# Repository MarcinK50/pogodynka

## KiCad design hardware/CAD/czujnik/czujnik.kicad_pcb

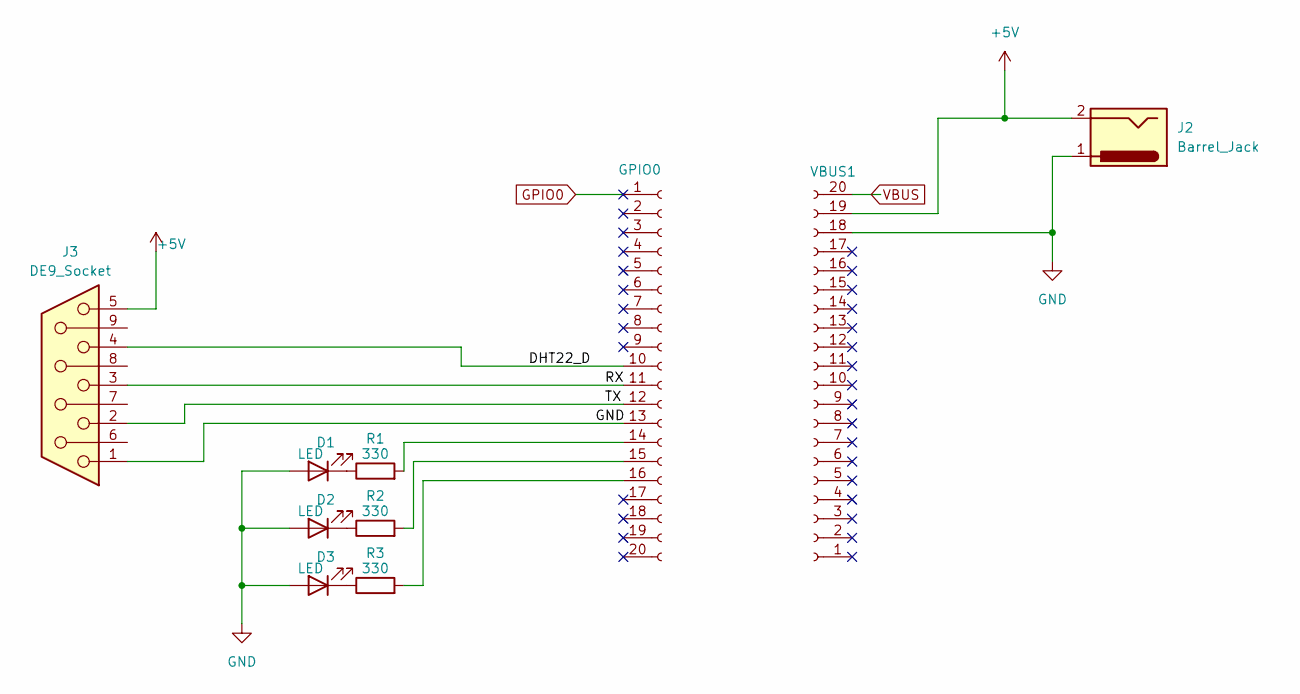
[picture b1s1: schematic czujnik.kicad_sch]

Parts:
D1, D2, D3: LED; LED_D3.0mm_Clear
GPIO0: Conn_01x20_Socket; PinSocket_1x20_P2.54mm_Vertical
J2: Barrel_Jack; BarrelJack_CUI_PJ-063AH_Horizontal_CircularHoles
J3: DE9_Socket; DSUB-9_Socket_Horizontal_P2.77x2.84mm_EdgePinOffset7.70mm_H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
R1, R2, R3: 330; R_Axial_DIN0207_L6.3mm_D2.5mm_P10.16mm_Horizontal
VBUS1: Conn_01x20_Socket; PinSocket_1x20_P2.54mm_Vertical

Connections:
+5V: J2.2, J3.5, VBUS1.19; also elsewhere on the board
/DHT22_D: GPIO0.10, J3.4
/RX: GPIO0.11, J3.3
/TX: GPIO0.12, J3.2
GND: D1.2 (A), D2.2 (A), D3.2 (A), GPIO0.13, J2.1, J3.1, VBUS1.18; also elsewhere on the board
GPIO0: GPIO0.1
unnamed: D1.1 (K), R1.1
unnamed: D2.1 (K), R2.1
unnamed: D3.1 (K), R3.1
unnamed: GPIO0.14, R1.2
unnamed: GPIO0.15, R2.2
unnamed: GPIO0.16, R3.2

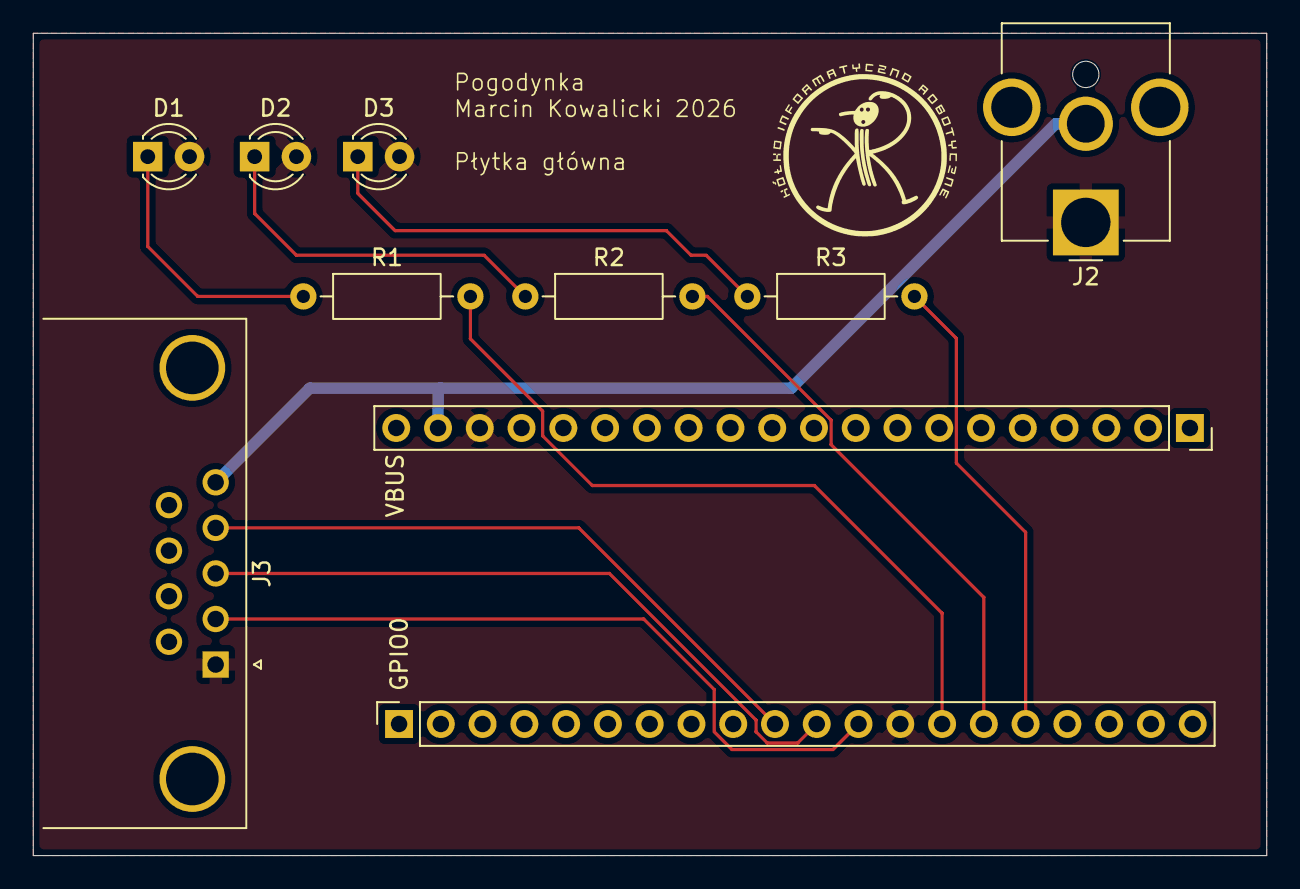
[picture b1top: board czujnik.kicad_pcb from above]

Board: 2 copper layers, 75.0 x 50.0 mm, 10 parts (0 on the bottom side), 11 nets.

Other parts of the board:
VBUS: Conn_01x20_Socket; PinSocket_1x20_P2.54mm_Vertical

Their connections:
+5V: VBUS.19; also elsewhere on the board
GND: VBUS.18; also elsewhere on the board

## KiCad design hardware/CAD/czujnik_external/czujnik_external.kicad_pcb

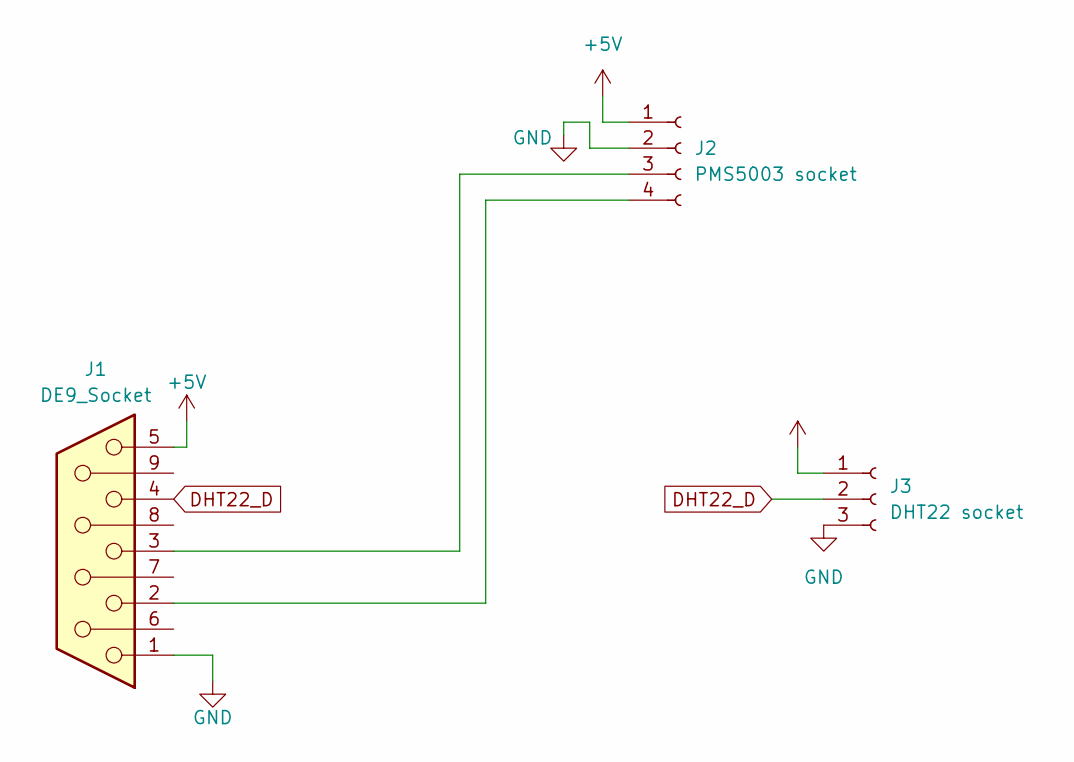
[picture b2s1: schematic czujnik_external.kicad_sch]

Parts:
J1: DE9_Socket; DSUB-9_Socket_Horizontal_P2.77x2.54mm_EdgePinOffset9.40mm
J2: PMS5003 socket; PinSocket_1x04_P2.54mm_Vertical
J3: DHT22 socket; PinSocket_1x03_P2.54mm_Vertical

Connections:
+5V: J1.5, J2.1, J3.1
DHT22_D: J1.4, J3.2
GND: J1.1, J2.2, J3.3
unnamed: J1.3, J2.3
unnamed: J1.2, J2.4

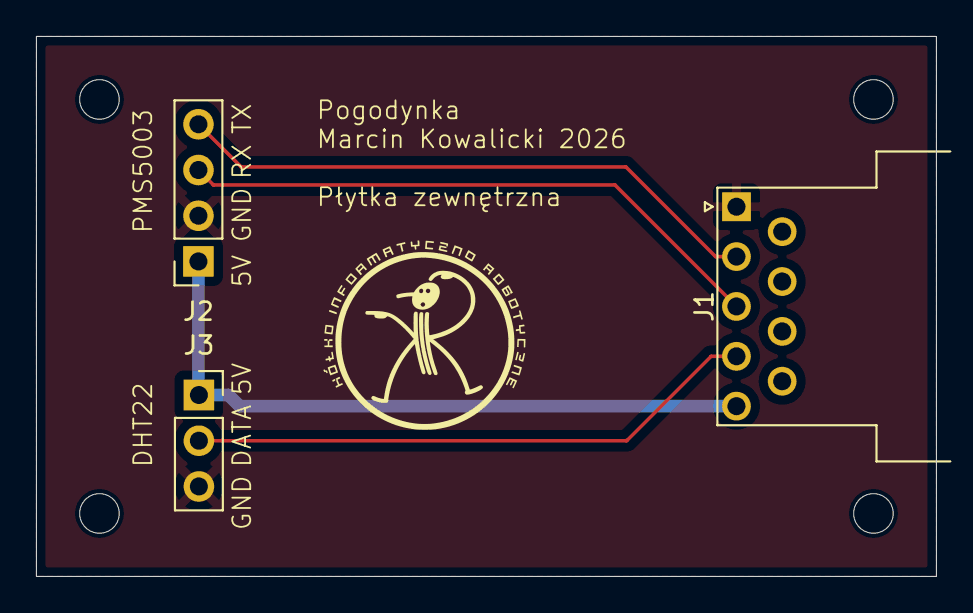
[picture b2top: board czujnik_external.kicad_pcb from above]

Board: 2 copper layers, 50.0 x 30.0 mm, 3 parts (0 on the bottom side), 5 nets.

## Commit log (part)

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2026-02-23 logging cleanup: remove unnecessary printing to console, add log level and log directory configuration
2026-02-28 config example file
2026-03-04 add calibration with ESA NASK script
2026-03-04 make device cover walls thinner
2026-03-10 Thinner walls for sensor cover
2026-03-11 new calibration data
2026-05-02 refactor PCBs, add gerber files
2026-05-05 add DB9 connectors to PCBs
2026-05-13 update sensor calibration data
2026-05-14 add missing +5V path to rpi on main PCB
2026-06-09 new device cover
2026-06-09 seperate parts of cover
